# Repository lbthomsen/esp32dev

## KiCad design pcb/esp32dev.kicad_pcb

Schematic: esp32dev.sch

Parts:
AE1: Texas_SWRA117D_2.4GHz_Right
C1, C2: 10uF; C_0805_2012Metric
C3, C4, C5, C6, C7, C8, C9, C14: 100nF; C_0402_1005Metric; LCSC C307331
C10, C11: 10pF; C_0402_1005Metric; LCSC C32949
C12, C13: NM; C_0603_1608Metric
D1: D_SOD-123; LCSC C8598
D2: WS2812; LED_WS2812C-2020; LCSC C965556
J1, J2: PinHeader_2x10_P2.54mm_Vertical
J3: USB-C; USB_C_Receptacle_HRO_TYPE-C-31-M-12; LCSC C165948
L1: 0R; L_0603_1608Metric; LCSC C21189
R1: 10k; R_0402_1005Metric; LCSC C25744
R2, R3: 22R; R_0402_1005Metric; LCSC C25092
R5, R6: 5.1k; R_0402_1005Metric; LCSC C25905
SW1, SW2: TS-1088R-02526
U1: ESP32-C3; QFN-32-1EP_5x5mm_P0.5mm_EP3.1x3.1mm_ThermalVias; LCSC C2838500
U2: AP1117-33; SOT-223-3_TabPin2
U3: W25Q128JVS; SOIC-8_5.23x5.23mm_P1.27mm; LCSC C97521
Y1: 40MHz; Crystal_SMD_3225-4Pin_3.2x2.5mm; LCSC C90924

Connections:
+3V3: C2.1, C3.1, C4.1, C5.1, C6.1, C7.1, C9.1, D2.4, R1.1, U1.2 (VDD3P3), U1.3 (VDD3P3), U1.11 (VDD3P3_RTC), U1.17 (VDD3P3_CPU), U1.31 (VDDA), U1.32 (VDDA), U2.2
+5V: D1.2, J3.A4, J3.A9, J3.B4, J3.B9
EN: C14.1, R1.2, SW1.2, U1.7 (EN)
F_CK: U1.21 (GPIO14/SPICS0), U3.6
F_CS: U1.20 (GPIO13/SPIWP), U3.1
F_DI: U1.22 (GPIO15/SPICLK), U3.5
F_DO: U1.23 (GPIO16/SPID), U3.2
GND: AE1.2, C1.2, C2.2, C3.2, C4.2, C5.2, C6.2, C7.2, C8.2, C9.2, C10.2, C11.2, C12.2, C13.2, C14.2, D2.2, J3.A1, J3.A12, J3.B1, J3.B12, J3.S1, R5.2, R6.2, SW1.1, U1.33 (GND), U2.1, U3.4, Y1.2, Y1.4
IO0: U1.4 (X32P)
IO1: U1.5 (X32N)
IO2: U1.6 (GPIO2)
IO3: U1.8 (GPIO3)
IO4_MTMS: U1.9 (GPIO4/MTMS)
IO5_MTDI: U1.10 (GPIO5/MTDI)
IO6_MTCK: U1.12 (GPIO6_MTCK)
IO7_MTDO: U1.13 (GPIO7/MTDO)
IO8: U1.14 (GPIO8)
IO9: U1.15 (GPIO9)
IO10: U1.16 (GPIO10)
IO13_F_WP: U3.3
IO18_DM: J2.9, J2.10, R2.2, U1.25 (GPIO18/USB_D-)
IO19_DP: J2.7, J2.8, R3.2, U1.26 (GPIO19/USB_D+)
IO20_U0RX: J2.5, J2.6, U1.27 (GPIO20/U0RXD)
IO21_U0TX: J2.3, J2.4, U1.28 (GPIO21/U0TXD)
unnamed: AE1.1, C12.1, L1.1
unnamed: C10.1, U1.29 (XN), Y1.1
unnamed: C11.1, U1.30 (XP), Y1.3
unnamed: C13.1, L1.2, U1.1 (LNA_IN)
unnamed: J1.1, J1.2
unnamed: J1.3, J1.4
unnamed: J1.5, J1.6
unnamed: J1.7, J1.8
unnamed: J1.9, J1.10
unnamed: J1.11, J1.12
unnamed: J1.13, J1.14
unnamed: J1.15, J1.16
unnamed: J1.17, J1.18
unnamed: J1.19, J1.20
unnamed: J2.1, J2.2
unnamed: J2.11, J2.12
unnamed: J2.13, J2.14
unnamed: J2.15, J2.16
unnamed: J2.17, J2.18
unnamed: J2.19, J2.20
unnamed: J3.A5, R6.1
unnamed: J3.A6, J3.B6, R3.1
unnamed: J3.A7, J3.B7, R2.1
unnamed: J3.B5, R5.1
VBUS: C1.1, D1.1, U2.3
VDD_SPI: C8.1, U1.18 (VDD_SPI), U3.8

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
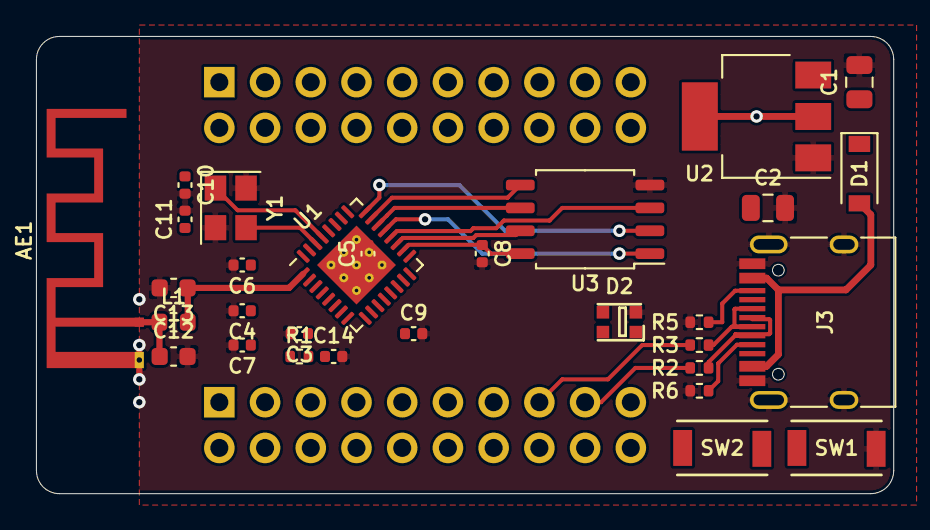
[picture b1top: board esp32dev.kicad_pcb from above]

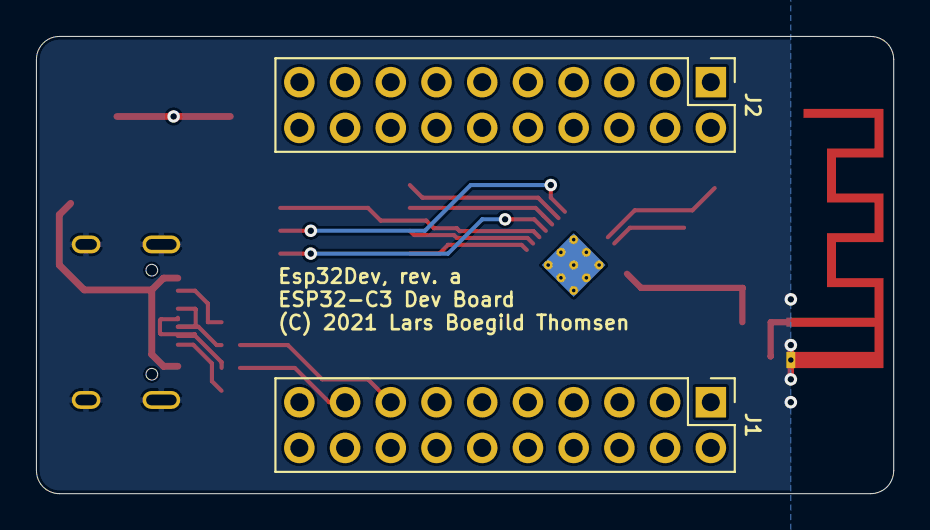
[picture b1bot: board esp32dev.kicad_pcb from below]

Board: 4 copper layers, 47.6 x 25.4 mm, 32 parts (2 on the bottom side), 39 nets.

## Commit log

2021-11-09 Hmmmm
2021-11-21 Hmmm

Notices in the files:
pcb/esp32dev.kicad_pcb:
(C) 2021 Lars Boegild Thomsen
